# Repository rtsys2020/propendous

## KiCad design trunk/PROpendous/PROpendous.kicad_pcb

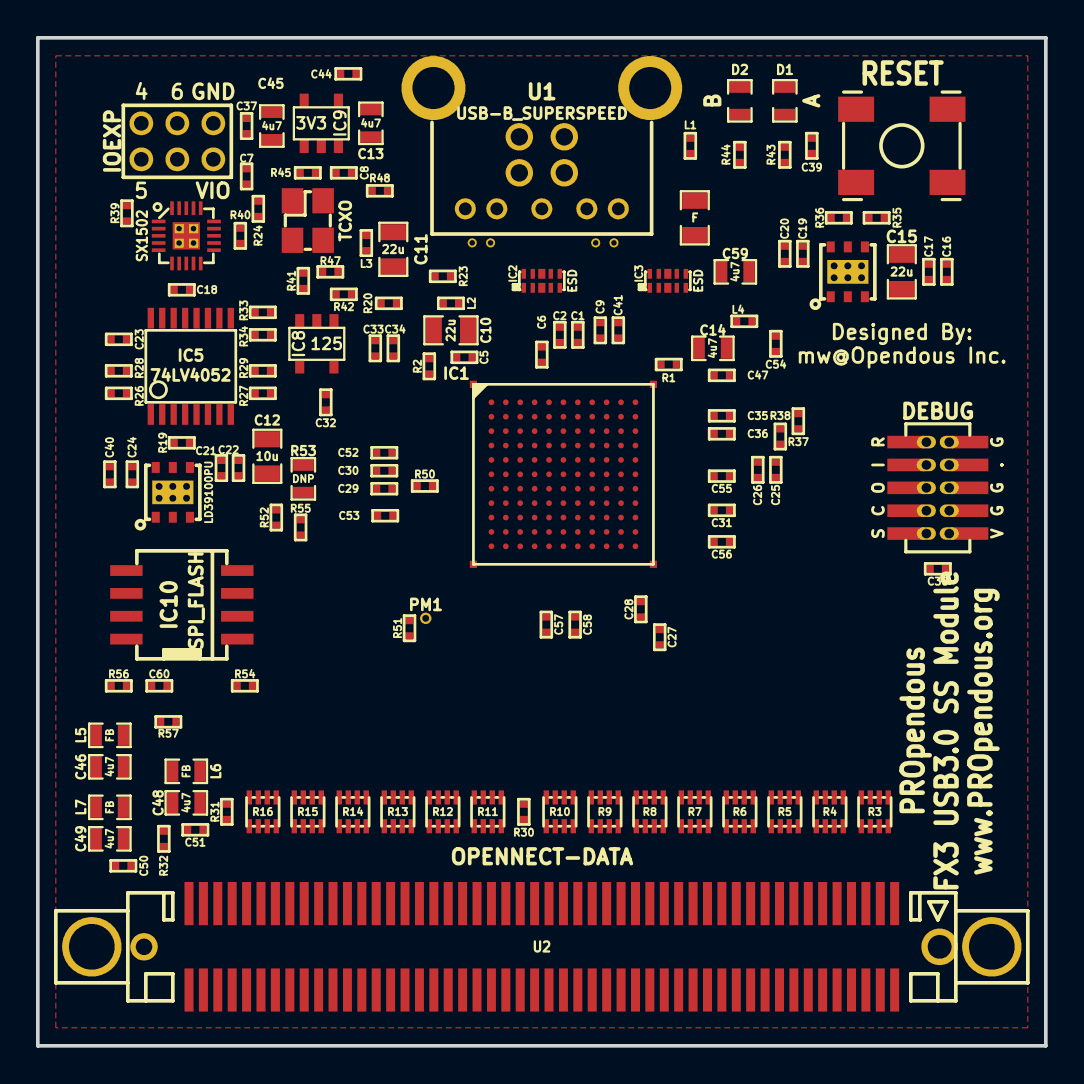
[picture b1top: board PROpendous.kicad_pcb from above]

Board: 4 copper layers, 56.0 x 56.0 mm, 137 parts (0 on the bottom side), 179 nets, no tracks yet.

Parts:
C1, C2, C5, C6, C7, C8, C17, C18, C19, C21, C23, C25, C27, C29, C31, C32, C33, C35, C37, C38, C39, C40, C41, C47, C50, C51, C52, C53, C54, C55, C56, C57, C58, C60: 0u1; 0402_Opendous_Labeled
C9, C16, C20, C22, C24, C26, C28, C30, C34, C36, C44: u01; 0402_Opendous_Labeled
C10, C11, C15: 22u; 0805_Opendous
C12: 10u; 0805_Opendous
C13, C14, C45, C46, C48, C49, C59: 4u7; 0603_Opendous_with_Label
D1: A; 0603_Opendous_with_Label
D2: B; 0603_Opendous_with_Label
F1: F; 0805_Opendous
IC1: CYUSB30XX-BZX; BGA121_0.8mmPitch
IC2, IC3: ESD; SON10_ESD_DQA
IC4, IC6: LD39100PU; DFN6_3x3mm_ST1L05B
IC5: 74LV4052; TSSOP16_DBQ
IC7: SX1502; QFN20_0.4mmPitch_SX150x
IC8: 125; SOT23-5
IC9: 3V3; SOT23-5
IC10: SPI_FLASH; SO8W_208mil_25FLASH
L1, L2, L3, L4: FB; 0402_Opendous_Labeled
L5, L6, L7: FB; 0603_Opendous_with_Label
P1: IOEXP; PIN_ARRAY_3x2_2mm
P2: PM1; 1Pin_15mil_VIA
R1: 6.04k; 0402_Opendous_Labeled
R2: 200; 0402_Opendous_Labeled
R3, R4, R5, R6, R7, R8, R9, R10, R11, R12, R13, R14, R15, R16: 22; SM0402_4Array
R19, R36: 47k; 0402_Opendous_Labeled
R20, R23, R24, R33, R34, R39, R40, R42, R45, R48, R50, R51, R52, R54, R56, R57: 10k; 0402_Opendous_Labeled
R26: 15k; 0402_Opendous_Labeled
R27: 22k; 0402_Opendous_Labeled
R28: 30k9; 0402_Opendous_Labeled
R29: 37k4; 0402_Opendous_Labeled
R30, R31, R32, R41, R47: 22; 0402_Opendous_Labeled
R35: 23k7; 0402_Opendous_Labeled
R37, R38: 2.2k; 0402_Opendous_Labeled
R43, R44: 1k; 0402_Opendous_Labeled
R53: DNP; 0603_Opendous_with_Label
R55: 100k; 0402_Opendous_Labeled
SW1: RESET; Switch_SMT_EVQ
U1: USB-B_SUPERSPEED; USB-B_USB3.0_SuperSpeed
U2: OPENNECT-DATA; DIL_6108x_BTB_Connector
U3: DEBUG; JTAG_Cortex
V1, V2, V3, V4: VIA; 1Pin_12mil_VIA
X1: TCXO; Crystal_3.2x2.5mm

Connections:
26MHz: IC8.4, R32.2
+3.3V: C8.1, C9.1, C37.1, C45.1, IC1.B6, IC9.5, L5.2, R20.2, R24.2, R45.2, R48.2, X1.4
+3.3V_BTB: C46.1, L5.1, U2.55
/26MHz_BTB: R32.1, U2.49
/Power/1Y0: IC5.1, R26.2
/Power/1Y1: IC5.5, R27.2
/Power/1Y2: IC5.2, R28.2
/Power/1Y3: IC5.4, R29.2
/Power/VIO_ADJ: IC4.5, IC5.3, R19.1
/System/125_A: IC8.2, R41.2
/System/Dm: IC1.A10, IC3.2, IC3.9, U1.2
/System/Dp: IC1.A9, IC3.1, IC3.10, U1.3
/System/IOEXP_nRESET: IC7.1, R39.1
/System/SSRXm: IC1.A3, IC2.1, IC2.10, U1.8, V1.1
/System/SSRXp: IC1.A4, IC2.2, IC2.9, U1.9, V2.1
/System/SSTXm: C1.1, IC1.A6
/System/SSTXm_AC: C1.2, IC2.5, IC2.6, U1.5, V3.1
/System/SSTXp: C2.1, IC1.A5
/System/SSTXp_AC: C2.2, IC2.4, IC2.7, U1.6, V4.1
/System/TCXO_EN: R45.1, X1.1
/System/TCXO_OUT: R41.1, R47.1, X1.3
/System/VBUS_F: F1.1, U1.1
AVDD: C14.1, C41.1, IC1.A7, L4.1
CLKIN: IC1.D7, R47.2
FSLC0: IC1.B2, R20.1
FSLC1: IC1.B4, R23.2
FSLC2: IC1.E6, R24.1
GND: C5.2, C6.2, C7.2, C8.2, C9.2, C10.2, C11.2, C12.2, C13.2, C14.2, C15.2, C16.2, C17.2, C18.2, C19.2, C20.2, C21.2, C22.2, C23.2, C24.2, C25.2, C26.2, C27.2, C28.2, C29.2, C30.2, C31.2, C32.2, C33.2, C34.2, C35.2, C36.2, C37.2, C38.2, C39.2, C40.2, C41.2, C44.2, C45.2, C46.2, C47.2, C48.2, C49.2, C50.2, C51.2, C52.2, C53.2, C54.2, C55.2, C56.2, C57.2, C58.2, C59.2, C60.2, IC1.A1, IC1.A8, IC1.B7, IC1.B8, IC1.B9, IC1.D8, IC1.E2, IC1.G1, IC1.G11, IC1.K3, IC1.K4, IC1.L1, IC1.L2, IC1.L3, IC1.L6, IC1.L11, IC2.3, IC2.8, IC3.3, IC3.8, IC4.2, IC4.7, IC5.6, IC5.7, IC5.8, IC5.13, IC6.2, IC6.7, IC7.8, IC7.18, IC8.3, IC9.2, IC10.4, L1.1, P1.5, R1.1, R2.1, R23.1, R26.1, R27.1, R28.1, R29.1, R36.1, R51.1, R53.1, R55.1, R57.1, SW1.1, U1.4, U1.7, U2.1, U2.4, U2.7, U2.10, U2.13, U2.16, U2.19, U2.22, U2.25, U2.27, U2.30, U2.33, U2.36, U2.39, U2.42, U2.45, U2.48, U2.50, U2.51, U2.54, U2.57, U2.60, U2.63, U2.66, U2.69, U2.72, U2.75, U2.78, U2.81, U2.84, U2.87, U2.90, U2.93, U2.96, U2.99, U2.100, U3.3, U3.5, U3.9, X1.2
GNDSHIELD: L1.2, U1.0
GPIO00: IC1.F10, R3.1
GPIO00-DQ00: R3.2, U2.2
GPIO01: IC1.F9, R3.3
GPIO01-DQ01: R3.4, U2.3
GPIO02: IC1.F7, R3.5
GPIO02-DQ02: R3.6, U2.98
GPIO03: IC1.G10, R3.7
GPIO03-DQ03: R3.8, U2.97
GPIO04: IC1.G9, R4.1
GPIO04-DQ04: R4.2, U2.5
GPIO05: IC1.F8, R4.3
GPIO05-DQ05: R4.4, U2.6
GPIO06: IC1.H10, R4.5
GPIO06-DQ06: R4.6, U2.95
GPIO07: IC1.H9, R4.7
GPIO07-DQ07: R4.8, U2.94
GPIO08: IC1.J10, R5.1
GPIO08-DQ08: R5.2, U2.8
GPIO09: IC1.J9, R5.3
GPIO09-DQ09: R5.4, U2.9
GPIO10: IC1.K11, R5.5
GPIO10-DQ10: R5.6, U2.92
GPIO11: IC1.L10, R5.7
GPIO11-DQ11: R5.8, U2.91
GPIO12: IC1.K10, R6.1
GPIO12-DQ12: R6.2, U2.11
GPIO13: IC1.K9, R6.3
GPIO13-DQ13: R6.4, U2.12
GPIO14: IC1.J8, R6.5
GPIO14-DQ14: R6.6, U2.89
GPIO15: IC1.G8, R6.7
GPIO15-DQ15: R6.8, U2.88
GPIO16: IC1.J6, R30.2
GPIO16-PCLK: R30.1, U2.26
GPIO17: IC1.K8, R11.1
GPIO17-CTL00: R11.2, U2.74
GPIO18: IC1.K7, R11.3
GPIO18-CTL01: R11.4, U2.73
GPIO19: IC1.J7, R11.5
GPIO19-CTL02: R11.6, U2.28
GPIO20: IC1.H7, R11.7
GPIO20-CTL03: R11.8, U2.29
GPIO21: IC1.G7, R12.1
GPIO21-CTL04: R12.2, U2.71
GPIO22: IC1.G6, R12.3
GPIO22-CTL05: R12.4, U2.70
GPIO23: IC1.K6, R12.5
GPIO23-CTL06: R12.6, U2.31
GPIO24: IC1.H8, R12.7
GPIO24-CTL07: R12.8, U2.32
GPIO25: IC1.G5, R13.1
GPIO25-CTL08: R13.2, U2.68
GPIO26: IC1.H6, R13.3
GPIO26-CTL09: R13.4, U2.67
GPIO27: IC1.K5, R13.5
GPIO27-CTL10: R13.6, U2.34
GPIO28: IC1.J5, R13.7
GPIO28-CTL11: R13.8, U2.35
GPIO29: IC1.H5, R14.1
GPIO29-CTL12: R14.2, U2.65
GPIO30-PMODE0: IC1.G4, R50.1
GPIO31-PMODE1: IC1.H4, P2.1
GPIO32-PMODE2: IC1.L4, R51.2
GPIO33: IC1.K2, R7.1
GPIO33-DQ16: R7.2, U2.14
GPIO34: IC1.J4, R7.3
GPIO34-DQ17: R7.4, U2.15
GPIO35: IC1.K1, R7.5
GPIO35-DQ18: R7.6, U2.86
GPIO36: IC1.J2, R7.7
GPIO36-DQ19: R7.8, U2.85
GPIO37: IC1.J3, R8.1
GPIO37-DQ20: R8.2, U2.17
GPIO38: IC1.J1, R8.3
GPIO38-DQ21: R8.4, U2.18
GPIO39: IC1.H2, R8.5
GPIO39-DQ22: R8.6, U2.83
GPIO40: IC1.H3, R8.7
GPIO40-DQ23: R8.8, U2.82
GPIO41: IC1.F4, R9.1
GPIO41-DQ24: R9.2, U2.20
GPIO42: IC1.G2, R9.3
GPIO42-DQ25: R9.4, U2.21
GPIO43: IC1.G3, R9.5
GPIO43-DQ26: R9.6, U2.80
GPIO44: IC1.F3, R9.7
GPIO44-DQ27: R9.8, U2.79
GPIO45: IC1.F2, R31.2, R57.2
GPIO45_BTB: R31.1, U2.56
GPIO46: IC1.F5, R10.1
GPIO46-DQ28: R10.2, U2.23
GPIO47: IC1.E1, R10.3
GPIO47-DQ29: R10.4, U2.24
GPIO48: IC1.E5, R10.5
GPIO48-DQ30: R10.6, U2.77
GPIO49: IC1.E4, R10.7
GPIO49-DQ31: R10.8, U2.76
GPIO50: IC1.D1, R14.5
GPIO50-I2S_CLK: R14.6, U2.37
GPIO51: IC1.D2, R14.7
GPIO51-I2S_SD: R14.8, U2.38
GPIO52: IC1.D3, R15.1
GPIO52-I2S_WS: R15.2, U2.62
GPIO53: IC1.D4, IC10.6, R15.7, R55.2
GPIO53-UART_RTS-SPI_SCK: R15.8, U2.41
GPIO54: IC1.C1, IC10.1, R15.5, R54.1
GPIO54-UART_CTS-SPI_nSS: R15.6, U2.40
GPIO55: IC1.C2, IC10.2, R16.1
GPIO55-UART_TX-SPI_MISO: R16.2, U2.59
GPIO56: IC1.D5, IC10.5, R16.3
GPIO56-UART_RX-SPI_MOSI: R16.4, U2.58
GPIO57: IC1.C4, R15.3
GPIO57-I2S_MCLK: R15.4, U2.61
GPIO58: IC1.D9, IC7.4, R16.5, R37.1
GPIO58-I2C_SCL: R16.6, U2.43
GPIO59: IC1.D10, IC7.2, R16.7, R38.1
GPIO59-I2C_SDA: R16.8, U2.44
IOEXP0: IC5.10, IC7.5, R34.1
IOEXP1: IC5.9, IC7.6, R33.1
IOEXP2: IC7.9, R43.1
IOEXP3: IC7.10, R44.1
IOEXP4: IC7.15, P1.1
IOEXP5: IC7.16, P1.2
IOEXP6: IC7.19, P1.3
IOEXP7: IC7.20, IC8.1, R42.1
unnamed: IC6.5, R35.1, R36.2
unnamed: C44.1, IC9.4
unnamed: D2.1, R44.2
unnamed: D1.1, R43.2
unnamed: IC7.12, R40.1
unnamed: IC10.7, R56.1
unnamed: IC3.4, IC3.7
R_USB2: IC1.C8, R1.2
R_USB3: IC1.B3, R2.2
SPI_nWP: IC10.3, R52.1, R53.2
TCK: IC1.F6, U3.4
TDI: IC1.E7, U3.8
TDO: IC1.C10, U3.6
TMS: IC1.E8, U3.2
U3RXVDDQ: C5.1, C10.1, IC1.A2, L2.1
U3TXVDDQ: C6.1, C11.1, IC1.B5, L3.1
VBUS: C13.1, C18.1, C19.1, C20.1, C23.1, C24.1, C25.1, C26.1, C40.1, C59.1, D1.2, D2.2, F1.2, IC1.E10, IC1.E11, IC3.5, IC3.6, IC4.1, IC4.6, IC5.16, IC6.1, IC6.6, IC7.7, IC9.1, IC9.3, L7.2, R33.2, R34.2
VBUS_BTB: C49.1, C50.1, L7.1, U2.52, U2.53
VDD_1V2: C15.1, C16.1, C17.1, C47.1, C52.1, C53.1, C54.1, C55.1, C56.1, C57.1, C58.1, IC1.B10, IC1.C3, IC1.E9, IC1.F11, IC1.H1, IC1.J11, IC1.L5, IC1.L7, IC6.4, L2.2, L3.2, L4.2, R35.2
VIO: C7.1, C12.1, C21.1, C22.1, C27.1, C28.1, C29.1, C30.1, C31.1, C32.1, C33.1, C34.1, C35.1, C36.1, C38.1, C60.1, IC1.B1, IC1.C11, IC1.E3, IC1.F1, IC1.H11, IC1.L9, IC4.4, IC7.14, IC7.17, IC8.5, IC10.8, L6.2, P1.6, R19.2, R37.2, R38.2, R39.2, R40.2, R42.2, R50.2, R52.2, R54.2, R56.2, U3.1
VIO_BTB: C48.1, C51.1, L6.1, U2.46, U2.47
nINT: IC1.L8, R14.3
nINT-CTL15: R14.4, U2.64
nRESET: C39.1, IC1.C5, R48.1, SW1.2
nTRST: IC1.B11, U3.10

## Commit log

2009-12-10 Initial directory structure.
2010-02-06 Added PRopendous-DIY hardware design files.
2010-04-06 Started PRopendous iMX233-based design.
2010-04-08 Renamed files.
2010-04-08 Updated files. DDR SDRAM schematic completed.
2010-04-17 Updated PROpendous i.MX233 project. DDR SDRAM layout is complete.
2010-04-20 Updated PROpendous project. Schematic is complete but not yet finalized. Layout partially complete.
2010-04-22 Minor update to schematic. Removed USB Power switch and added some notes.
2010-04-24 Updated PROpendous Project. PCB layout is nearing completion.
2010-04-25 Updated layout.
2010-04-25 Updated layout. Extended expansion connector and moved microSD.
2010-04-26 First revision of i.MX233-based PROpendous board is complete.
2010-04-27 Updated i.MX233-based PROpendous board with EEPROM to fix Freescale Errata #2229.
2010-05-06 Added Gerber PCB manufacturing files. Started Bill Of Materials.
2010-05-06 Update Bill of Materials.
2010-05-06 Completed Bill of Materials.
2010-05-06 Minor update.
2010-05-18 Updated design files. Added picture of finished PCB.
2010-05-18 Added PROpendous assembly instructions.
2010-05-18 Updated PROpendous design and manufacturing files.
2010-05-31 Updated PROpendous design with correct FSUSB20 footprint. Added pictures of minimally assembled board and related testing.
2010-06-05 Updated PROpendous Manufacturing Gerbers to the latest revision.
2010-06-07 Updated PROpendous with correct I2C EEPROM address. Added pictures of the LPC3130 based PROpendous-DIY.
2010-06-21 Switch to ceramic capacitors for bulk decoupling which are less expensive than similarly low-ESR tantalum capacitors.
2010-06-21 Updated Gerber fabrication files to latest revision.
2010-09-28 Updated the design. JTAG header now includes VDD_XTAL and SSP1_Detect. 1.8" LCD has been removed and LCD backlight control is now connected to GPMI_CE1n. The clock signals for the DDR SDRAM are now t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
2010-10-12 Removed LPC313x version of the PROpendous. Focus has for a while been on the i.MX233 version. LPC313x design is now available at: http://code.google.com/p/opendous/source/browse/trunk/Abandoned_Desig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
2010-10-13 Replaced 3M 2908-05WB-MG microSD connector with the better stocked Amphenol 101-00303-68.
2010-10-13 Updated Bill of Materials with new microSD connector.
2010-10-20 Updated PROpendous design with minor correction to silkscreen and two more bypass capacitors for the microSD connector. Also added Buttons Module design files.
2010-10-21 Updated PROpendous design. PWM2-GPMI_RDY3 now controls the LCD backlight and GPMI_CE1n now controls USB Host enable. The function of these pins was switched as PWM2 makes more sense as a backlight co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
2010-10-31 Minor update of Connectors_JTAG sheet with note about updated microSD connector part number.
2010-11-18 Added pictures of a fully assembled board.
2012-10-03 Minor directory renaming and removed individual schematic PDFs.
2012-10-03 Updated all design files with CC0 Public Domain License. Added single PDF version of schematic. Updated the layout's GND fill to solid instead of thermal. Kept previous revision Gerbers.
2013-10-24 Archived PROpendous i.MX233 Project Files.
2013-10-24 Removed i.MX233 picture files.
2013-10-24 Removed i.MX233 Project Files.
2013-10-24 Added PROpendous FX3 ( CYUSB301x-BZX) USB3.0 SuperSpeed Module project files.
2015-08-08 Migrating wiki contents from Google Code
